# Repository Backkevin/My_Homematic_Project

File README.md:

# My_Homematic_Project

 My Homematic boards

-----------------------------------------------------------------

+ [HB-Dis-EP-42BW](https://github.com/Backkevin/My_Homematic_Project/tree/master/HB-Dis-EP-42BW)
+ [Nachbau von Jérôme](https://github.com/jp112sdl/HB-Dis-EP-42BW)
	+ V1.0
		* Work 50%
		* Partlist not OK
		* 230VAC Version
		* [INO FILE](https://github.com/Backkevin/My_Homematic_Project/tree/master/HB-Dis-EP-42BW/INO/HB-Dis-EP-42BW)
		* [GERBER FILES](https://github.com/Backkevin/My_Homematic_Project/tree/master/HB-Dis-EP-42BW/GERBER%20FILES)
		* [EAGLE FILES](https://github.com/Backkevin/My_Homematic_Project/tree/master/HB-Dis-EP-42BW/EAGLE)
		
	+ Work in progress !
>

-----------------------------------------------------------------

+ [HB-OU-MP3-LED](https://github.com/Backkevin/My_Homematic_Project/tree/master/HB-OU-MP3-LED)
+ [Nachbau von Jérôme](https://github.com/jp112sdl/HB-OU-MP3-LED)
	+ V2.1
		* Work 85%
		* Partlist OK
		* 230VAC Version
		* [INO FILE](https://github.com/Backkevin/My_Homematic_Project/tree/master/HB-OU-MP3-LED/INO/HB-OU-MP3-LED)
		* [GERBER FILES](https://github.com/Backkevin/My_Homematic_Project/tree/master/HB-OU-MP3-LED/GERBER%20FILES)
		* [EAGLE FILES](https://github.com/Backkevin/My_Homematic_Project/tree/master/HB-OU-MP3-LED/EAGLE)
		
	+ Work in progress !
>

-----------------------------------------------------------------

+ [HB-UNI-SenAct-4-4-RC](https://github.com/Backkevin/My_Homematic_Project/tree/master/HB-UNI-SenAct-4-4-RC)
+ [Nachbau von Ronny](https://github.com/ronnythomas/HB-UNI-SenAct-4-4-Hutschiene)
	+ V3.0
		* Work 100%
		* Partlist OK
		* 230VAC Version
		* [INO FILE](https://github.com/Backkevin/My_Homematic_Project/tree/master/HB-UNI-SenAct-4-4-RC/INO/HB-UNI-SenAct-4-4-RC)
		* [GERBER FILES](https://github.com/Backkevin/My_Homematic_Project/tree/master/HB-UNI-SenAct-4-4-RC/GERBER%20FILES)
		* [EAGLE FILES](https://github.com/Backkevin/My_Homematic_Project/tree/master/HB-UNI-SenAct-4-4-RC/EAGLE)
		
	+ Work in progress !
>

-----------------------------------------------------------------

+ [HB-UNI-SenAct-8-8-RC](https://github.com/Backkevin/My_Homematic_Project/tree/master/HB-UNI-SenAct-8-8-RC)
+ [Nachbau von Ronny](https://github.com/ronnythomas/HB-UNI-SenAct-8-8-Hutschiene)
	+ V2.1
		* Work 85%
		* Partlist OK
		* [INO FILE](https://github.com/Backkevin/My_Homematic_Project/tree/master/HB-UNI-SenAct-8-8-RC/INO/HB-UNI-SenAct-8-8-RC)
		* [GERBER FILES](https://github.com/Backkevin/My_Homematic_Project/tree/master/HB-UNI-SenAct-8-8-RC/GERBER%20FILES)
		* [EAGLE FILES](https://github.com/Backkevin/My_Homematic_Project/tree/master/HB-UNI-SenAct-8-8-RC/EAGLE)
		
	+ Work in progress !
>

-----------------------------------------------------------------

+ [HB-UNI-SEN-CAP-MOIST](https://github.com/Backkevin/My_Homematic_Project/tree/master/HB-UNI-SEN-CAP-MOIST)
+ [Nachbau von Jérôme](https://github.com/jp112sdl/HB-UNI-Sen-CAP-MOIST)
     + V1.2
		* Work 75%
		* Partlist not OK
		* 230VAC Version
		* [INO FILE](https://github.com/Backkevin/My_Homematic_Project/tree/master/HB-UNI-SEN-CAP-MOIST/INO/HB-UNI-SEN-CAP-MOIST)
		* [GERBER FILES](https://github.com/Backkevin/My_Homematic_Project/tree/master/HB-UNI-SEN-CAP-MOIST/GERBER%20FILES)
		* [EAGLE FILES](https://github.com/Backkevin/My_Homematic_Project/tree/master/HB-UNI-SEN-CAP-MOIST/EAGLE)		
		
	+ Work in progress !
>

+ [Nachbau von technikkram](https://technikkram.net/2019/05/anleitung-diy-feuchtigkeitssensor-fuer-gartenbewaesserung-bausatz-homematic)
	+ V0.5
		* Work 25%
		* Solar Version
		* Partlist not OK	
			
	+ Work in progress !
>

-----------------------------------------------------------------

+ [HB-UNI-SEN-PHO](https://github.com/Backkevin/My_Homematic_Project/tree/master/HB-UNI-SEN-PHO)
+ [Eigenbau]
	+ V1.0
		* Work 25%
		* Partlist not OK
		* 230VAC Version
		* [INO FILE](https://github.com/Backkevin/My_Homematic_Project/tree/master/HB-UNI-SEN-PHO/INO/HB-UNI-SEN-PHO)
		* [GERBER FILES](https://github.com/Backkevin/My_Homematic_Project/tree/master/HB-UNI-SEN-PHO/GERBER%20FILES)
		* [EAGLE FILES](https://github.com/Backkevin/My_Homematic_Project/tree/master/HB-UNI-SEN-PHO/EAGLE)
		
	+ Work in progress !
>

-----------------------------------------------------------------

+ [HB-UNI-Sen-RFID-RC](https://github.com/Backkevin/My_Homematic_Project/tree/master/HB-UNI-Sen-RFID-RC)
+ [Nachbau von Jérôme](https://github.com/jp112sdl/HB-UNI-Sen-RFID-RC)
	+ V1.0
		* Work 25%
		* Partlist not OK
		* 230VAC Version
		* [INO FILE](https://github.com/Backkevin/My_Homematic_Project/tree/master/HB-UNI-Sen-RFID-RC/INO/HB-UNI-Sen-RFID-RC)
		* [GERBER FILES](https://github.com/Backkevin/My_Homematic_Project/tree/master/HB-UNI-Sen-RFID-RC/GERBER%20FILES)
		* [EAGLE FILES](https://github.com/Backkevin/My_Homematic_Project/tree/master/HB-UNI-Sen-RFID-RC/EAGLE)
		
	+ Work in progress !
>

-----------------------------------------------------------------

+ [HB-UNI-Sen-TEMP-DS18B20](https://github.com/Backkevin/My_Homematic_Project/tree/master/HB-UNI-Sen-TEMP-DS18B20)
+ [Nachbau von Jérôme](https://github.com/jp112sdl/HB-UNI-Sen-TEMP-DS18B20)
	+ V1.0
		* Work 75%
		* Partlist not OK
		* 230VAC Version
		* [INO FILE](https://github.com/Backkevin/My_Homematic_Project/tree/master/HB-UNI-Sen-TEMP-DS18B20/INO/HB-UNI-Sen-TEMP-DS18B20)
		* [GERBER FILES](https://github.com/Backkevin/My_Homematic_Project/tree/master/HB-UNI-Sen-TEMP-DS18B20/GERBER%20FILES)
		* [EAGLE FILES](https://github.com/Backkevin/My_Homematic_Project/tree/master/HB-UNI-Sen-TEMP-DS18B20/EAGLE)
		
	+ Work in progress !
>

-----------------------------------------------------------------

+ [HB-UNI-Sen-WEIGHT](https://github.com/Backkevin/My_Homematic_Project/tree/master/HB-UNI-Sen-WEIGHT)
+ [Nachbau von Jérôme](https://github.com/jp112sdl/HB-UNI-Sen-WEIGHT)
	+ V1.0
		* Work 50%
		* Partlist not OK
		* 230VAC Version
		* [INO FILE](https://github.com/Backkevin/My_Homematic_Project/tree/master/HB-UNI-Sen-WEIGHT/INO/HB-UNI-Sen-WEIGHT)
		* [GERBER FILES](https://github.com/Backkevin/My_Homematic_Project/tree/master/HB-UNI-Sen-WEIGHT/GERBER%20FILES)
		* [EAGLE FILES](https://github.com/Backkevin/My_Homematic_Project/tree/master/HB-UNI-Sen-WEIGHT/EAGLE)
		
	+ Work in progress !
>

-----------------------------------------------------------------

+ [HM-ES-PMSw1-Pl_GosundSP1](https://github.com/Backkevin/My_Homematic_Project/tree/master/HM-ES-PMSw1-Pl_GosundSP1)
+ [Nachbau von Jérôme](https://github.com/jp112sdl/Beispiel_AskSinPP/tree/master/examples/HM-ES-PMSw1-Pl_GosundSP1)
	+ V1.3
		* Work 50%
		* Partlist not OK
		* 230VAC Version
		* [INO FILE](https://github.com/Backkevin/My_Homematic_Project/tree/master/HM-ES-PMSw1-Pl_GosundSP1/INO/HM-ES-PMSw1-Pl_GosundSP1)
		* [GERBER FILES](https://github.com/Backkevin/My_Homematic_Project/tree/master/HM-ES-PMSw1-Pl_GosundSP1/GERBER%20FILES)
		* [EAGLE FILES](https://github.com/Backkevin/My_Homematic_Project/tree/master/HM-ES-PMSw1-Pl_GosundSP1/EAGLE)
		
	+ Work in progress !
>

-----------------------------------------------------------------

+ [HM-SEC-MDIR](https://github.com/Backkevin/My_Homematic_Project/tree/master/HM-SEC-MDIR)
+ [Nachbau von Jérôme](https://asksinpp.de/Projekte/jan/HM-SEC-MDIR/)
	+ V0.0
		* Work 0%
		* Partlist not OK
		* 230VAC Version
		* [INO FILE](https://github.com/Backkevin/My_Homematic_Project/tree/master/HM-SEC-MDIR/INO/HM-SEC-MDIR)
		* [GERBER FILES](https://github.com/Backkevin/My_Homematic_Project/tree/master/HM-SEC-MDIR/GERBER%20FILES)
		* [EAGLE FILES](https://github.com/Backkevin/My_Homematic_Project/tree/master/HM-SEC-MDIR/EAGLE)
		
	+ Work in progress !
>

-----------------------------------------------------------------

+ [HM-MOUSETRAP](https://github.com/Backkevin/My_Homematic_Project/tree/master/HM-MOUSETRAP)
+ [Eigenbau]
	+ V0.5
		* Work 25%
		* Battery Version
		* Partlist not OK
		* [STL Parts not OK](https://github.com/Backkevin/My_Homematic_Project/tree/master/HM-MOUSETRAP/STL%20FILES)
		* [INO FILE](https://github.com/Backkevin/My_Homematic_Project/tree/master/HM-MOUSETRAP/HM-MOUSETRAP)
		* [GERBER FILES](https://github.com/Backkevin/My_Homematic_Project/tree/master/HM-MOUSETRAP/GERBER%20FILES)
		* [EAGLE FILES](https://github.com/Backkevin/My_Homematic_Project/tree/master/HM-MOUSETRAP/EAGLE)
		
	+ Work in progress !
>

-----------------------------------------------------------------

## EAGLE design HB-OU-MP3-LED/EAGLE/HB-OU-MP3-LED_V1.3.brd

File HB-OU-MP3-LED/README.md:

# HB-OU-MP3-LED

+ HB-OU-MP3-LED
	+ V2.1
		* Work 85%
		* 230VAC Version
		* Partlist OK
	+ Work in progress !
>

### Partslist 230VAC Version
                    
  Part Name   |      PIC      |   Part Info   | Part Quantity |   Part Link 
------------- | ------------- | ------------- | ------------- | -------------
Arduino||Arduino Pro Mini 8Mhz 3.3V|1|[Links](https://de.aliexpress.com/item/32863952987.html?spm=a2g0s.9042311.0.0.27424c4d2YDzey)
CC1101||CC1101 Funkmodul|1|[Links](https://de.aliexpress.com/item/32924239954.html?spm=a2g0s.9042311.0.0.27424c4dO9ofu2)
Config,S1 - S4||Taster 6x6|5|[Links](https://de.aliexpress.com/item/32912263133.html?spm=a2g0s.9042311.0.0.2cb44c4dtuowdv)
LED1||LED 3mm|1|[Links](https://de.aliexpress.com/item/32844298998.html?spm=a2g0s.9042311.0.0.27424c4dBW9kvr)
HLK-5M05||HLK-PM01|1|[Links](https://de.aliexpress.com/item/32705471039.html?spm=a2g0s.9042311.0.0.2cb44c4dtuowdv)
F1,F2||Sicherungshalter|2|[Links](https://de.aliexpress.com/item/32817849786.html?spm=a2g0o.productlist.0.0.260073beDSkClD&algo_pvid=51b52a6f-dc94-4152-9721-98bffea40076&algo_expid=51b52a6f-dc94-4152-9721-98bffea40076-1&btsid=c94e558f-368d-470b-a49c-61c69230d3d9&ws_ab_test=searchweb0_0,searchweb201602_2,searchweb201603_52)
R5,R6||470 Ohm Widerstand|2|[Links](https://de.aliexpress.com/item/32475181535.html?spm=a2g0o.productlist.0.0.d4fa8034p2AKck&s=p&algo_pvid=4976c9e3-6165-4df4-b127-6d9845fdbe12&algo_expid=4976c9e3-6165-4df4-b127-6d9845fdbe12-1&btsid=7a52ff49-9ff4-47d2-965f-007ad481e8b7&ws_ab_test=searchweb0_0,searchweb201602_2,searchweb201603_52)
230V,HP||Wannenstecker für AKL 249, 2-pol, RM5,08|2|[Links](https://www.reichelt.de/wannenstecker-fuer-akl-249-2-pol-rm5-08-akl-230-02-p36701.html?)
RL1||Wannenstecker für AKL 249, 3-pol, RM5,08|1|[Links](https://www.reichelt.de/wannenstecker-fuer-akl-249-3-pol-rm5-08-akl-230-03-p36702.html?)
RL1||relais srd-05vdc|1|[Links](https://de.aliexpress.com/item/32695798177.html?spm=a2g0o.productlist.0.0.46db7659cuB4fB&algo_pvid=f16bd12e)
Arduino||Pin Header Streifen 12 Pin|2|[Links](https://de.aliexpress.com/item/32904918519.html?spm=a2g0s.9042311.0.0.27424c4dCsKCBi)
CC1101||Stiftleiste 20 polig, vergoldet, Raster 2,00mm|1|[Links](https://secure.reichelt.com/lu/de/stiftleiste-20-pol-vergoldet-bkl-10120400-p235635.html?)
C1||50V10UF|1|[Links](https://de.aliexpress.com/item/32741687066.html?spm=a2g0o.productlist.0.0.4d225216N68Cr1&algo_pvid=dbcb75f4-e623-4355-8aa4-ccd3a7b65d32&algo_expid=dbcb75f4-e623-4355-8aa4-ccd3a7b65d32-3&btsid=a9b8176e-1372-45d7-a781-8d3fc9fab8e5&ws_ab_test=searchweb0_0,searchweb201602_2,searchweb201603_52)
Arduino||Jumper|1|[Links](https://de.aliexpress.com/item/32873263301.html?spm=a2g0o.productlist.0.0.18ea263dluRsmQ&algo_pvid=b495ebad-e4de-4809-a086-8143c1f9f12b&algo_expid=b495ebad-e4de-4809-a086-8143c1f9f12b-2&btsid=53bb7c29-6fd7-4471-b8c4-bc2766b36d10&ws_ab_test=searchweb0_0,searchweb201602_2,searchweb201603_52)
RGB||RGB LED Ring 12 Bits WS2812|1|[Links](https://de.aliexpress.com/item/32668049892.html?spm=a2g0s.9042311.0.0.27424c4dPLs0SQ)
-||Speicher Karte|1|[Links](https://de.aliexpress.com/item/4000019505752.html?gps-id=detail404&scm=1007.16891.96945.0&scm_id=1007.16891.96945.0&scm-url=1007.16891.96945.0&pvid=281247d2-c3f0-421b-91d9-69d1a5222bc4)
DFP||DFPlayer|1|[Links](https://de.aliexpress.com/item/32750446150.html?spm=a2g0s.9042311.0.0.5daf4c4dPxve55)
R2,R3,R4||1K Ohm Widerstand|3|[Links](https://de.aliexpress.com/item/32475181535.html?spm=a2g0o.productlist.0.0.d4fa8034p2AKck&s=p&algo_pvid=4976c9e3-6165-4df4-b127-6d9845fdbe12&algo_expid=4976c9e3-6165-4df4-b127-6d9845fdbe12-1&btsid=7a52ff49-9ff4-47d2-965f-007ad481e8b7&ws_ab_test=searchweb0_0,searchweb201602_2,searchweb201603_52)
R5||10K Ohm Widerstand|1|[Links](https://de.aliexpress.com/item/32475181535.html?spm=a2g0o.productlist.0.0.d4fa8034p2AKck&s=p&algo_pvid=4976c9e3-6165-4df4-b127-6d9845fdbe12&algo_expid=4976c9e3-6165-4df4-b127-6d9845fdbe12-1&btsid=7a52ff49-9ff4-47d2-965f-007ad481e8b7&ws_ab_test=searchweb0_0,searchweb201602_2,searchweb201603_52)
D1||1N4007|1|[Links](https://de.aliexpress.com/item/32224555821.html?spm=a2g0o.productlist.0.0.6ff73c09BmbGrH&algo_pvid=0cedbead-f9df-432f-a6b8-7889af0010ea&algo_expid=0cedbead-f9df-432f-a6b8-7889af0010ea-0&btsid=9d3b584d-5993-438c-bda5-70eb309fc04f&ws_ab_test=searchweb0_0,searchweb201602_2,searchweb201603_52)
BC327||BC327|1|[Links](https://de.aliexpress.com/item/32694388198.html?spm=a2g0o.productlist.0.0.490b435cYT2xvd&algo_pvid=df4c990b-2fc8-4f12-b155-a7185f993490&algo_expid=df4c990b-2fc8-4f12-b155-a7185f993490-2&btsid=ff438d29-ef2e-467f-babc-337d85f9c973&ws_ab_test=searchweb0_0,searchweb201602_2,searchweb201603_52)
PC817||PC817|1|[Links](https://de.aliexpress.com/item/32835155712.html?spm=a2g0s.9042311.0.0.27424c4dyoIvyA)
-|-|-|-
OPTIONAL||FT232RL USB zu TTL Serielle Adapter|1|[Links](https://de.aliexpress.com/item/32846166237.html?spm=a2g0s.9042311.0.0.27424c4dQGznlY)
OPTIONAL||28X40 MM 4R 3 W lautsprecher|1|[Links](https://de.aliexpress.com/item/32765499972.html?spm=a2g0s.9042311.0.0.27424c4dS08YRH)

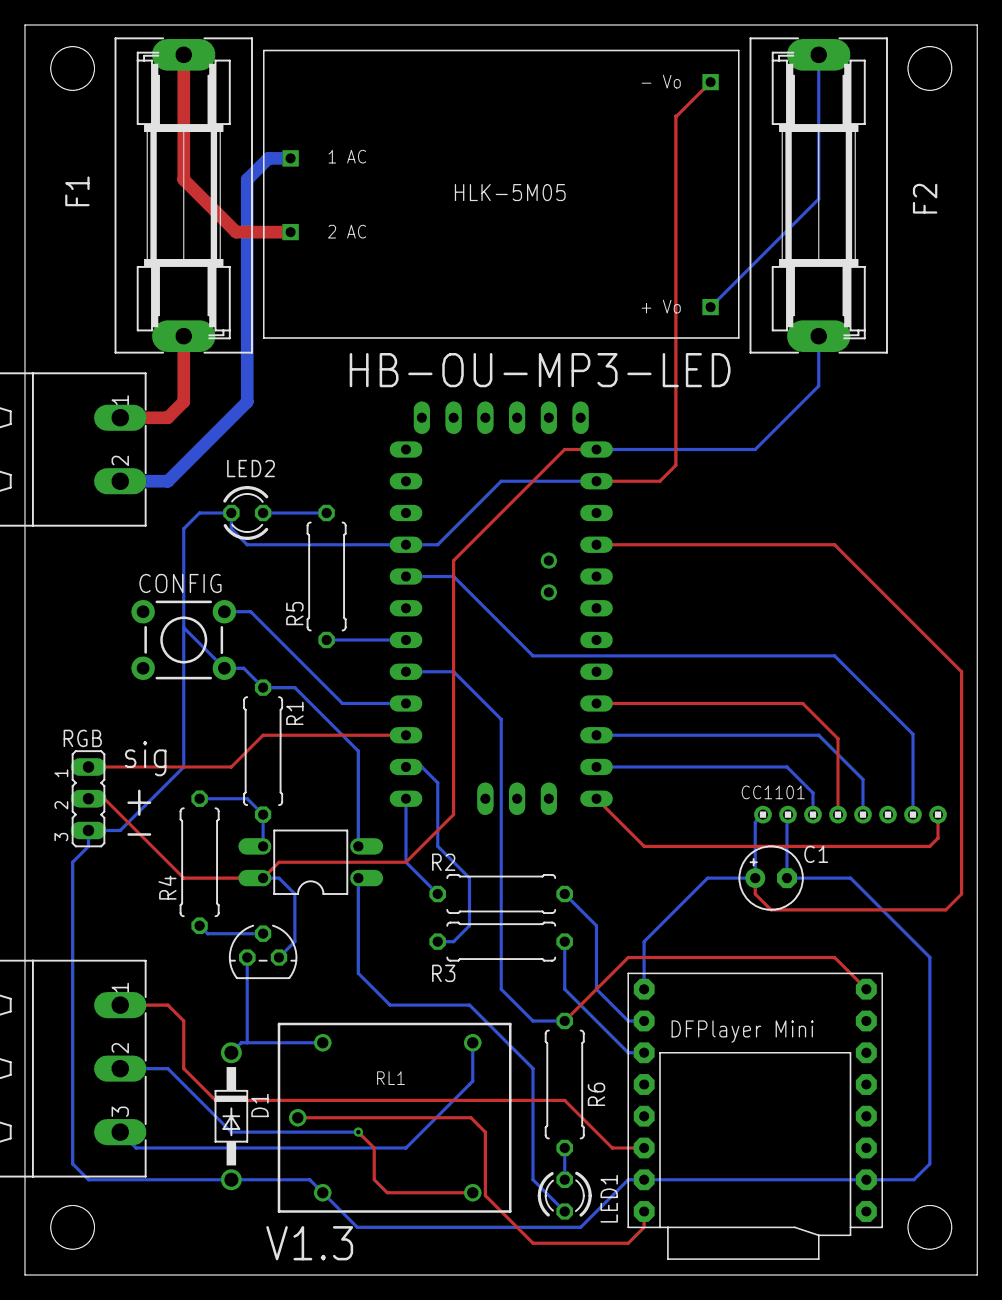
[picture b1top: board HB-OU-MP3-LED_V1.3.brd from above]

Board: 2 copper layers, 76.2 x 100.0 mm, 23 parts (0 on the bottom side), 30 nets.

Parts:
C1: E2,5-5
CONFIG: MOMENTARY-SWITCH-SPST-PTH-6.0MM-KIT; TACTILE_SWITCH_PTH_6.0MM_KIT
D1: 1N4007; DO41-10
F1, F2: SH22,5A
LED1, LED2: LED3MM
OK1: PC817; DIL04
Q1: BC327; TO92
R1: 10K; 0309/10
R2, R3, R4: 1K; 0309/10
R5, R6: 470; 0309/10
RGB: JP2
RL1: RELAYPTH; SRD-05VDC-SL-C
U$1: 1X8
U$2: ABK-PRO-MINI
U$3: 5VDC/5W; HLK-5M05
U$4: DFPLAYER
X1: MSTBA2
X3: MSTBA3

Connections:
CSN: U$1.8, U$2.D10
GDO0: U$1.7, U$2.D2
GND: C1.-, CONFIG.1, D1.A, LED2.A, OK1.2, R1.1, RGB.3, RL1.COIL0, U$1.2, U$2.GND, U$2.GND1, U$3.3, U$4.GND_1, U$4.GND_2
unnamed: RGB.1, U$2.D7
unnamed: CONFIG.3, U$2.D6
unnamed: R2.2, U$2.D9
unnamed: R3.2, U$2.D8
unnamed: R6.1, U$2.D5, U$4.BUSY
unnamed: U$4.SPK1, X3.1
unnamed: RL1.SWCOMMON, U$4.SPK2
unnamed: LED1.A, R6.2
unnamed: F1.1, X1.1
unnamed: F2.1, U$3.4
unnamed: U$3.2, X1.2
unnamed: D1.C, Q1.3, RL1.COIL1
unnamed: RL1.SWCLOSED, X3.2
unnamed: R2.1, U$4.RX
unnamed: R3.1, U$4.TX
unnamed: OK1.3, R1.2, R4.1
unnamed: R5.1, U$2.D4
unnamed: LED2.K, R5.2
unnamed: F1.2, U$3.1
unnamed: RL1.SWOPEN, X3.3
unnamed: LED1.K, OK1.1
unnamed: Q1.2, R4.2
RAW: F2.2, OK1.4, Q1.1, RGB.2, U$2.RAW
SCLK: U$1.4, U$2.D13
SI: U$1.3, U$2.D11
SO: U$1.5, U$2.D12
VCC: C1.+, U$1.1, U$2.VCC, U$4.VCC

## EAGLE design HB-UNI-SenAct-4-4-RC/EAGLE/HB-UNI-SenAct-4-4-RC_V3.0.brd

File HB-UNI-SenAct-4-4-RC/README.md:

# HB-UNI-SenAct-4-4-RC

+ HB-UNI-SenAct-4-4-RC
	+ V3.0
		* Work 100%
		* 230VAC Version
		* Partlist OK
	+ Work in progress !

>

### Partslist 230VAC Version
                    
  Part Name   |      PIC      |   Part Info   | Part Quantity |   Part Link 
------------- | ------------- | ------------- | ------------- | -------------
Arduino||Arduino Pro Mini 8Mhz 3.3V|1|[Links](https://de.aliexpress.com/item/32863952987.html?spm=a2g0s.9042311.0.0.27424c4d2YDzey)
CC1101||CC1101 Funkmodul|1|[Links](https://de.aliexpress.com/item/32924239954.html?spm=a2g0s.9042311.0.0.27424c4dO9ofu2)
Config,S1 - S4||Taster 6x6|5|[Links](https://de.aliexpress.com/item/32912263133.html?spm=a2g0s.9042311.0.0.2cb44c4dtuowdv)
LED1 - LED5||LED 3mm|5|[Links](https://de.aliexpress.com/item/32844298998.html?spm=a2g0s.9042311.0.0.27424c4dBW9kvr)
HLK-5M05||HLK-PM01|1|[Links](https://de.aliexpress.com/item/32705471039.html?spm=a2g0s.9042311.0.0.2cb44c4dtuowdv)
F1,F2||Sicherungshalter|2|[Links](https://de.aliexpress.com/item/32817849786.html?spm=a2g0o.productlist.0.0.260073beDSkClD&algo_pvid=51b52a6f-dc94-4152-9721-98bffea40076&algo_expid=51b52a6f-dc94-4152-9721-98bffea40076-1&btsid=c94e558f-368d-470b-a49c-61c69230d3d9&ws_ab_test=searchweb0_0,searchweb201602_2,searchweb201603_52)
R1 - R5||470 Ohm Widerstand|5|[Links](https://de.aliexpress.com/item/32475181535.html?spm=a2g0o.productlist.0.0.d4fa8034p2AKck&s=p&algo_pvid=4976c9e3-6165-4df4-b127-6d9845fdbe12&algo_expid=4976c9e3-6165-4df4-b127-6d9845fdbe12-1&btsid=7a52ff49-9ff4-47d2-965f-007ad481e8b7&ws_ab_test=searchweb0_0,searchweb201602_2,searchweb201603_52)
230V,S1 - S4||Wannenstecker für AKL 249, 2-pol, RM5,08|5|[Links](https://www.reichelt.de/wannenstecker-fuer-akl-249-2-pol-rm5-08-akl-230-02-p36701.html?)
RL1 - RL4||Wannenstecker für AKL 249, 3-pol, RM5,08|4|[Links](https://www.reichelt.de/wannenstecker-fuer-akl-249-3-pol-rm5-08-akl-230-03-p36702.html?)
RL1 - RL4||relais srd-05vdc|4|[Links](https://de.aliexpress.com/item/32695798177.html?spm=a2g0o.productlist.0.0.46db7659cuB4fB&algo_pvid=f16bd12e)
Arduino||Pin Header Streifen 12 Pin|2|[Links](https://de.aliexpress.com/item/32904918519.html?spm=a2g0s.9042311.0.0.27424c4dCsKCBi)
CC1101||Stiftleiste 20 polig, vergoldet, Raster 2,00mm|1|[Links](https://secure.reichelt.com/lu/de/stiftleiste-20-pol-vergoldet-bkl-10120400-p235635.html?)
ULN2803||ULN2803A|1|[Links](https://de.aliexpress.com/item/32881616806.html?spm=a2g0o.productlist.0.0.27805012dPDPf4&algo_pvid=2ce275e5-5ca6-4441-a1e3-fb3df6923537&algo_expid=2ce275e5-5ca6-4441-a1e3-fb3df6923537-0&btsid=14cad76a-3ab1-4af8-af47-443eb0bf5dae&ws_ab_test=searchweb0_0,searchweb201602_2,searchweb201603_52)
C1||50V10UF|1|[Links](https://de.aliexpress.com/item/32741687066.html?spm=a2g0o.productlist.0.0.4d225216N68Cr1&algo_pvid=dbcb75f4-e623-4355-8aa4-ccd3a7b65d32&algo_expid=dbcb75f4-e623-4355-8aa4-ccd3a7b65d32-3&btsid=a9b8176e-1372-45d7-a781-8d3fc9fab8e5&ws_ab_test=searchweb0_0,searchweb201602_2,searchweb201603_52)
Sabotage,Arduino||Jumper|1|[Links](https://de.aliexpress.com/item/32873263301.html?spm=a2g0o.productlist.0.0.18ea263dluRsmQ&algo_pvid=b495ebad-e4de-4809-a086-8143c1f9f12b&algo_expid=b495ebad-e4de-4809-a086-8143c1f9f12b-2&btsid=53bb7c29-6fd7-4471-b8c4-bc2766b36d10&ws_ab_test=searchweb0_0,searchweb201602_2,searchweb201603_52)
-|-|-|-
OPTIONAL||FT232RL USB zu TTL Serielle Adapter|1|[Links](https://de.aliexpress.com/item/32846166237.html?spm=a2g0s.9042311.0.0.27424c4dQGznlY)

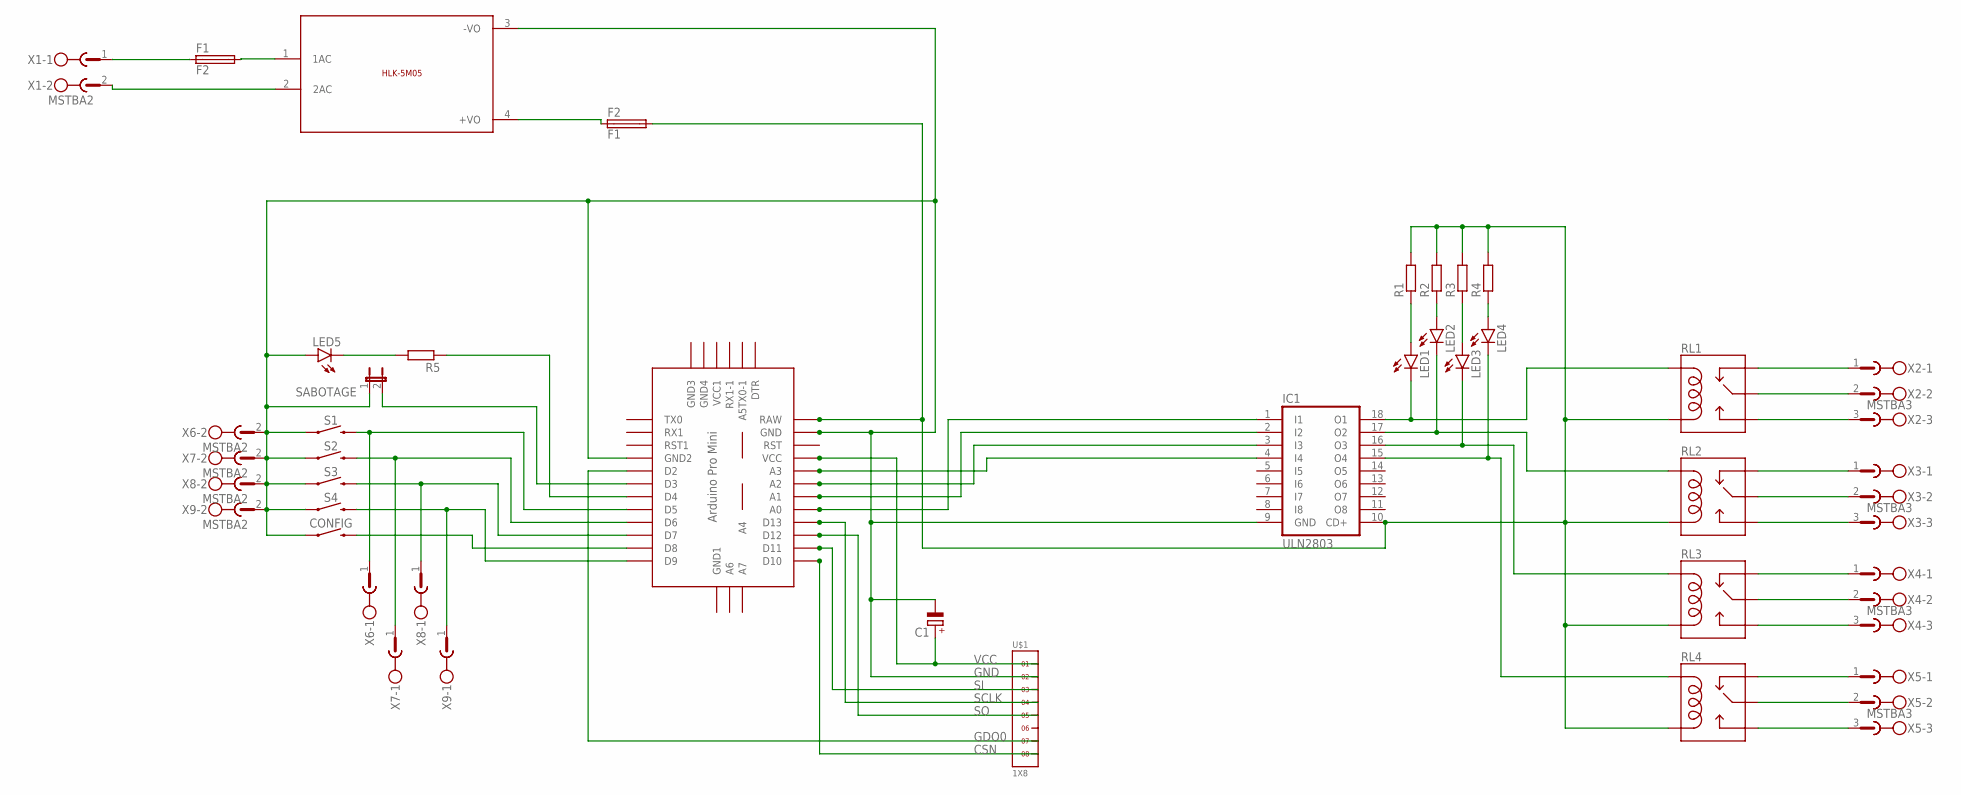
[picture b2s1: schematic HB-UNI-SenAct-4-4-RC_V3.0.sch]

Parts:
C1: CPOL-EUE2.5-5; E2,5-5
CONFIG: MOMENTARY-SWITCH-SPST-PTH-6.0MM-KIT; TACTILE_SWITCH_PTH_6.0MM_KIT
F1: F2; SH22,5A
F2: F1; SH22,5A
IC1: ULN2803; DIL18
LED1, LED2, LED3, LED4, LED5: LED3MM
R1, R2, R3, R4, R5: R-EU_0309/10; 0309/10
RL1, RL3, RL4: RELAYPTH; SRD-05VDC-SL-C
RL2: RL2; SRD-05VDC-SL-C
S1: MOMENTARY-SWITCH-SPST-PTH-6.0MM; TACTILE_SWITCH_PTH_6.0MM
S2, S3, S4: MOMENTARY-SWITCH-SPST-PTH-6.0MM-KIT; TACTILE_SWITCH_PTH_6.0MM_KIT
SABOTAGE: JP1E; JP1
U$1: 1X8
U$2: ABK-PRO-MINI
U$3: 5VDC/5W; HLK-5M05
X1, X6, X7, X8, X9: MSTBA2
X2, X3, X4, X5: MSTBA3

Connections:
CSN: U$1.8, U$2.D10
GDO0: U$1.7, U$2.D2
GND: C1.-, CONFIG.1, IC1.9 (GND), LED5.A, S1.1, S2.1, S3.1, S4.1, SABOTAGE.1, U$1.2, U$2.GND, U$2.GND1 (GND2), U$3.3 (-VO), X6.2, X7.2, X8.2, X9.2
unnamed: IC1.1 (I1), U$2.A0
unnamed: IC1.2 (I2), U$2.A1
unnamed: IC1.3 (I3), U$2.A2
unnamed: IC1.4 (I4), U$2.A3
unnamed: LED1.A, R1.1
unnamed: LED2.A, R2.1
unnamed: LED3.A, R3.1
unnamed: LED4.A, R4.1
unnamed: F1.1, X1.1
unnamed: F2.1, U$3.4 (+VO)
unnamed: U$3.2 (2AC), X1.2
unnamed: S1.3 (2), U$2.D5, X6.1
unnamed: S2.3 (2), U$2.D6, X7.1
unnamed: S3.3 (2), U$2.D7, X8.1
unnamed: S4.3 (2), U$2.D9, X9.1
unnamed: CONFIG.3 (2), U$2.D8
unnamed: R5.1, U$2.D4
unnamed: LED5.K (C), R5.2
unnamed: F1.2, U$3.1 (1AC)
unnamed: SABOTAGE.2, U$2.D3
unnamed: RL3.SWCLOSED (SWCLOSE), X4.1
unnamed: RL4.SWCOMMON, X5.2
unnamed: RL3.SWOPEN, X4.3
unnamed: F2.2, IC1.10 (CD+), R1.2, R2.2, R3.2, R4.2, RL1.COIL0, RL2.COIL0, RL3.COIL0, RL4.COIL0, U$2.RAW
unnamed: RL4.SWCLOSED (SWCLOSE), X5.1
unnamed: RL3.SWCOMMON, X4.2
unnamed: RL4.SWOPEN, X5.3
unnamed: RL2.SWOPEN, X3.3
unnamed: RL2.SWCOMMON, X3.2
unnamed: RL2.SWCLOSED (SWCLOSE), X3.1
unnamed: RL1.SWOPEN, X2.3
unnamed: RL1.SWCOMMON, X2.2
unnamed: RL1.SWCLOSED (SWCLOSE), X2.1
unnamed: IC1.18 (O1), LED1.K (C), RL1.COIL1
unnamed: IC1.17 (O2), LED2.K (C), RL2.COIL1
unnamed: IC1.16 (O3), LED3.K (C), RL3.COIL1
unnamed: IC1.15 (O4), LED4.K (C), RL4.COIL1
SCLK: U$1.4, U$2.D13
SI: U$1.3, U$2.D11
SO: U$1.5, U$2.D12
VCC: C1.+, U$1.1, U$2.VCC

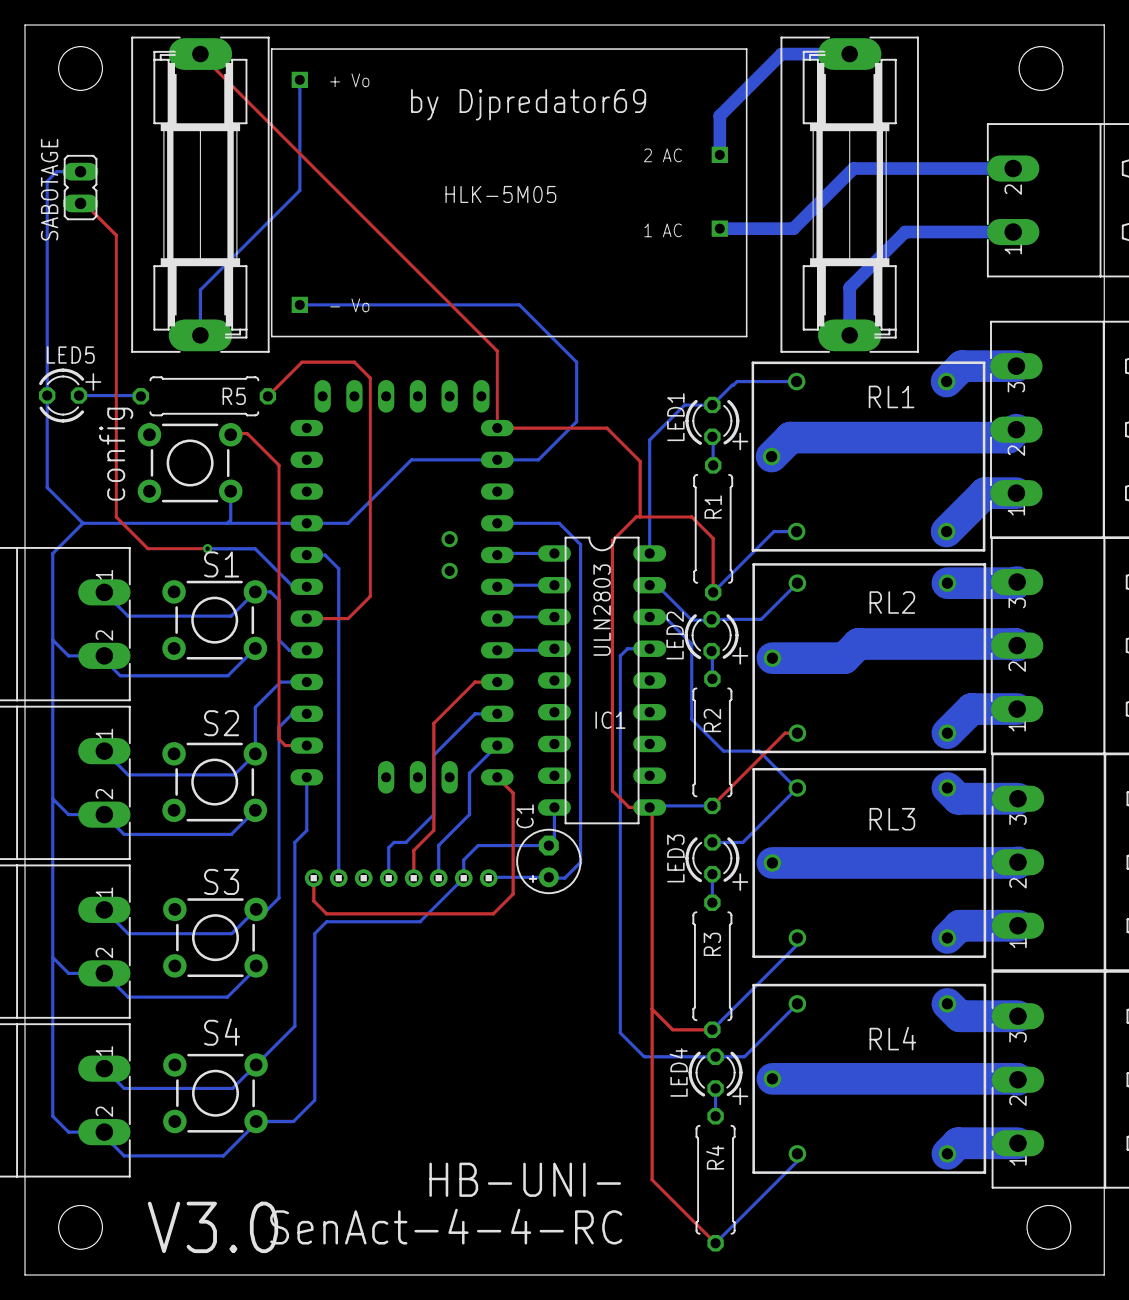
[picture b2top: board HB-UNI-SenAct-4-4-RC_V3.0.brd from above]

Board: 2 copper layers, 86.3 x 100.0 mm, 36 parts (0 on the bottom side), 44 nets.

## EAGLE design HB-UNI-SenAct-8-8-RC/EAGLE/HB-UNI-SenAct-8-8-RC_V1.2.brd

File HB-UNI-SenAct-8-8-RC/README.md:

# HB-UNI-SenAct-8-8-RC

+ HB-UNI-SenAct-8-8-RC
	+ V2.1
		* Work 85%
		* 230VAC Version
		* Partlist OK
	+ Work in progress !
>

### Partslist 230VAC Version
                    
  Part Name   |      PIC      |   Part Info   | Part Quantity |   Part Link 
------------- | ------------- | ------------- | ------------- | -------------
Arduino||Arduino Pro Mini 8Mhz 3.3V|1|[Links](https://de.aliexpress.com/item/32863952987.html?spm=a2g0s.9042311.0.0.27424c4d2YDzey)
CC1101||CC1101 Funkmodul|1|[Links](https://de.aliexpress.com/item/32924239954.html?spm=a2g0s.9042311.0.0.27424c4dO9ofu2)
Config,S1 - S8||Taster 6x6|9|[Links](https://de.aliexpress.com/item/32912263133.html?spm=a2g0s.9042311.0.0.2cb44c4dtuowdv)
LED1 - LED9||LED 3mm|9|[Links](https://de.aliexpress.com/item/32844298998.html?spm=a2g0s.9042311.0.0.27424c4dBW9kvr)
HLK-5M05||HLK-PM01|1|[Links](https://de.aliexpress.com/item/32705471039.html?spm=a2g0s.9042311.0.0.2cb44c4dtuowdv)
F1,F2||Sicherungshalter|2|[Links](https://de.aliexpress.com/item/32817849786.html?spm=a2g0o.productlist.0.0.260073beDSkClD&algo_pvid=51b52a6f-dc94-4152-9721-98bffea40076&algo_expid=51b52a6f-dc94-4152-9721-98bffea40076-1&btsid=c94e558f-368d-470b-a49c-61c69230d3d9&ws_ab_test=searchweb0_0,searchweb201602_2,searchweb201603_52)
R1 - R9||470 Ohm Widerstand|9|[Links](https://de.aliexpress.com/item/32475181535.html?spm=a2g0o.productlist.0.0.d4fa8034p2AKck&s=p&algo_pvid=4976c9e3-6165-4df4-b127-6d9845fdbe12&algo_expid=4976c9e3-6165-4df4-b127-6d9845fdbe12-1&btsid=7a52ff49-9ff4-47d2-965f-007ad481e8b7&ws_ab_test=searchweb0_0,searchweb201602_2,searchweb201603_52)
230V||Wannenstecker für AKL 249, 2-pol, RM5,08|1|[Links](https://www.reichelt.de/wannenstecker-fuer-akl-249-2-pol-rm5-08-akl-230-02-p36701.html?)
RL1 - RL8||Wannenstecker für AKL 249, 3-pol, RM5,08|8|[Links](https://www.reichelt.de/wannenstecker-fuer-akl-249-3-pol-rm5-08-akl-230-03-p36702.html?)
RL1 - RL8||relais srd-05vdc|8|[Links](https://de.aliexpress.com/item/32695798177.html?spm=a2g0o.productlist.0.0.46db7659cuB4fB&algo_pvid=f16bd12e)
Arduino||Pin Header Streifen 12 Pin|3|[Links](https://de.aliexpress.com/item/32904918519.html?spm=a2g0s.9042311.0.0.27424c4dCsKCBi)
CC1101||Stiftleiste 20 polig, vergoldet, Raster 2,00mm|1|[Links](https://secure.reichelt.com/lu/de/stiftleiste-20-pol-vergoldet-bkl-10120400-p235635.html?)
74AC540N||74AC540N|1|[Links](https://de.aliexpress.com/item/32962771569.html?spm=a2g0s.9042311.0.0.27424c4d9oXxJ5)
PCF8574||PCF8574|1|[Links](https://de.aliexpress.com/item/32933373566.html?spm=a2g0o.productlist.0.0.64a84f64Lvqpim&algo_pvid=cbe97703-3691-461b-ab85-9e0ba62d57db&algo_expid=cbe97703-3691-461b-ab85-9e0ba62d57db-1&btsid=dcfb9457-b3f3-4e03-af0e-92040a947379&ws_ab_test=searchweb0_0,searchweb201602_2,searchweb201603_52)
ULN2803||ULN2803A|1|[Links](https://de.aliexpress.com/item/32881616806.html?spm=a2g0o.productlist.0.0.27805012dPDPf4&algo_pvid=2ce275e5-5ca6-4441-a1e3-fb3df6923537&algo_expid=2ce275e5-5ca6-4441-a1e3-fb3df6923537-0&btsid=14cad76a-3ab1-4af8-af47-443eb0bf5dae&ws_ab_test=searchweb0_0,searchweb201602_2,searchweb201603_52)
C1||50V10UF|1|[Links](https://de.aliexpress.com/item/32741687066.html?spm=a2g0o.productlist.0.0.4d225216N68Cr1&algo_pvid=dbcb75f4-e623-4355-8aa4-ccd3a7b65d32&algo_expid=dbcb75f4-e623-4355-8aa4-ccd3a7b65d32-3&btsid=a9b8176e-1372-45d7-a781-8d3fc9fab8e5&ws_ab_test=searchweb0_0,searchweb201602_2,searchweb201603_52)
Sabotage,Arduino||Jumper|2|[Links](https://de.aliexpress.com/item/32873263301.html?spm=a2g0o.productlist.0.0.18ea263dluRsmQ&algo_pvid=b495ebad-e4de-4809-a086-8143c1f9f12b&algo_expid=b495ebad-e4de-4809-a086-8143c1f9f12b-2&btsid=53bb7c29-6fd7-4471-b8c4-bc2766b36d10&ws_ab_test=searchweb0_0,searchweb201602_2,searchweb201603_52)
-|-|-|-
OPTIONAL||FT232RL USB zu TTL Serielle Adapter|1|[Links](https://de.aliexpress.com/item/32846166237.html?spm=a2g0s.9042311.0.0.27424c4dQGznlY)

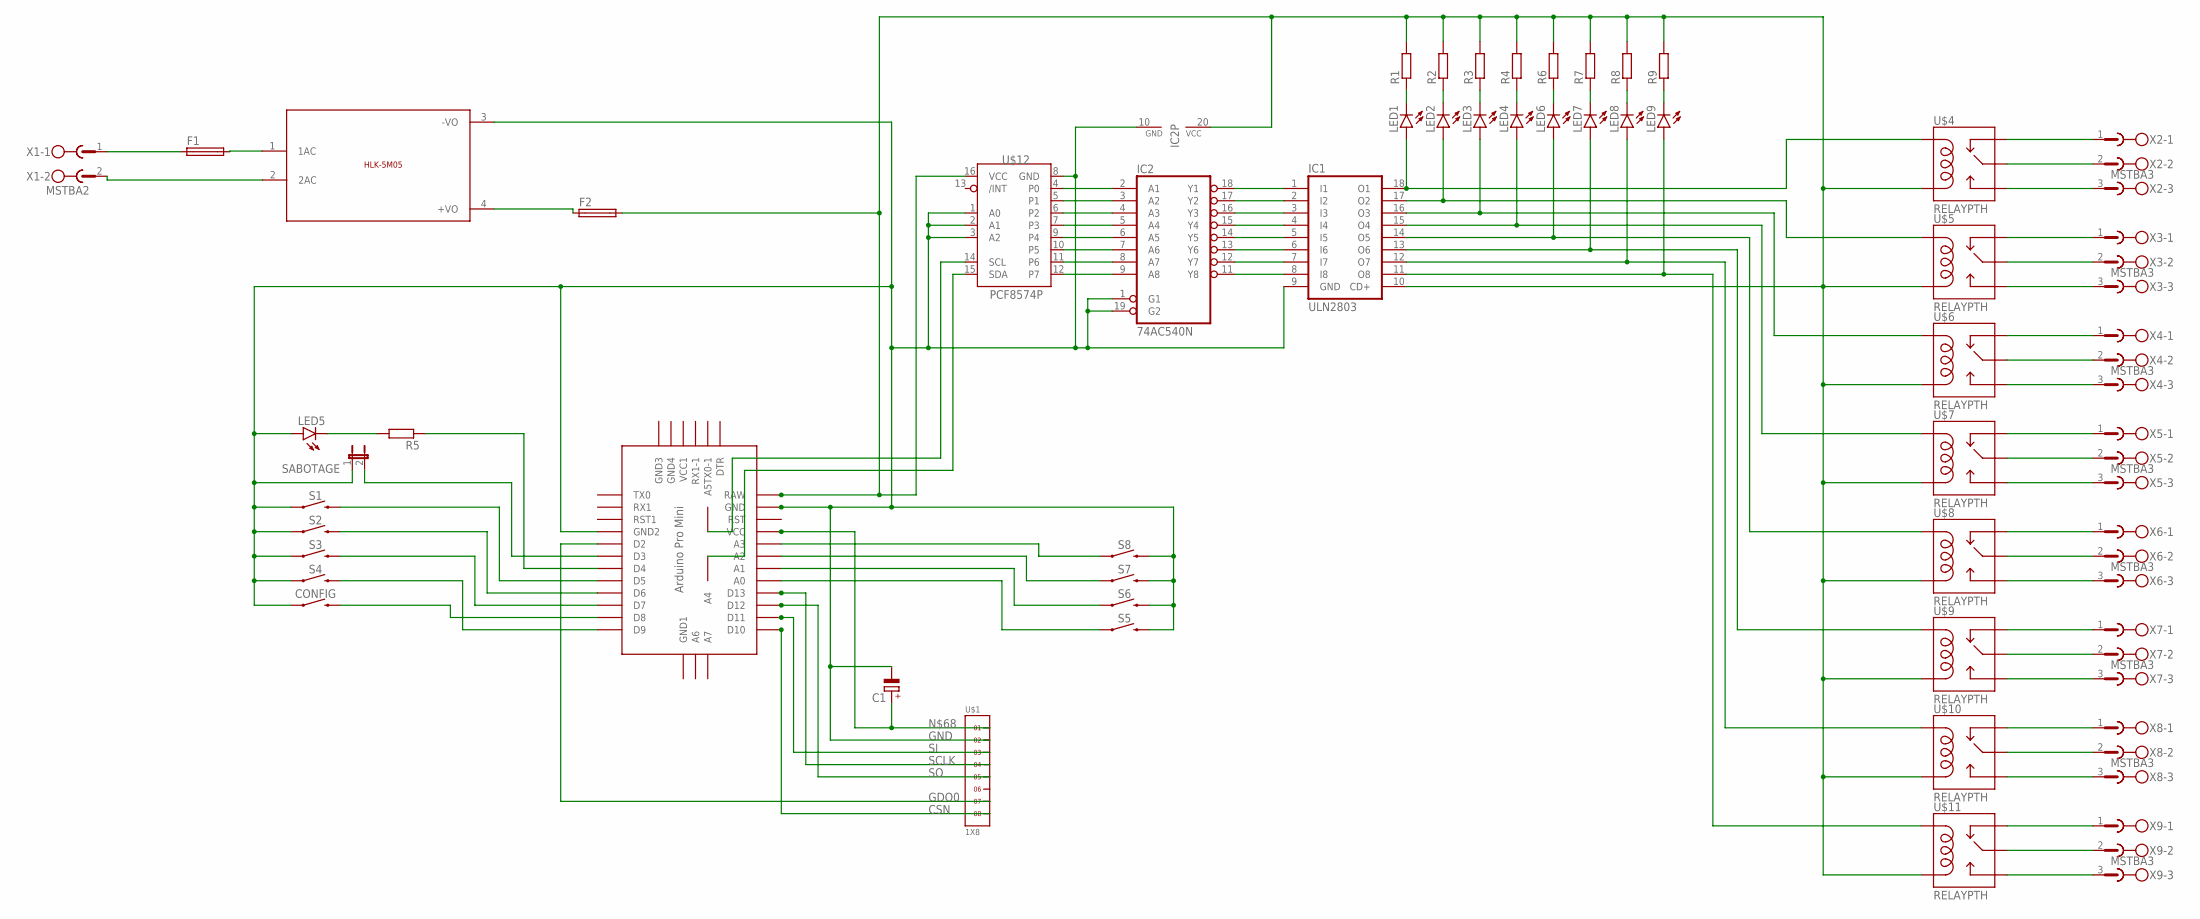
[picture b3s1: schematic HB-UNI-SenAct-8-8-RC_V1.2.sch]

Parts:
C1: CPOL-EUE2.5-5; E2,5-5
CONFIG: MOMENTARY-SWITCH-SPST-PTH-6.0MM-KIT; TACTILE_SWITCH_PTH_6.0MM_KIT
F1, F2: SH22,5A
IC1: ULN2803; DIL18
IC2: 74AC540N; DIL20
LED1, LED2, LED3, LED4, LED5, LED6, LED7, LED8, LED9: LED3MM
R1, R2, R3, R4, R5, R6, R7, R8, R9: R-EU_0309/10; 0309/10
S1: MOMENTARY-SWITCH-SPST-PTH-6.0MM; TACTILE_SWITCH_PTH_6.0MM
S2, S3, S4, S5, S6, S7, S8: MOMENTARY-SWITCH-SPST-PTH-6.0MM-KIT; TACTILE_SWITCH_PTH_6.0MM_KIT
SABOTAGE: JP1E; JP1
U$1: 1X8
U$2: ABK-PRO-MINI
U$3: 5VDC/5W; HLK-5M05
U$4, U$5, U$6, U$7, U$8, U$9, U$10, U$11: RELAYPTH; SRD-05VDC-SL-C
U$12: PCF8574P; DIL16
X1: MSTBA2
X2, X3, X4, X5, X6, X7, X8, X9: MSTBA3

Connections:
CSN: U$1.8, U$2.D10
GDO0: U$1.7, U$2.D2
GND: C1.-, CONFIG.1, IC1.9 (GND), IC2.1 (G1), IC2.10 (GND), IC2.19 (G2), LED5.A, S1.1, S2.1, S3.1, S4.1, S5.3 (2), S6.3 (2), S7.3 (2), S8.3 (2), SABOTAGE.1, U$1.2, U$2.GND, U$2.GND1 (GND2), U$3.3 (-VO), U$12.1 (A0), U$12.2 (A1), U$12.3 (A2), U$12.8 (GND)
unnamed: IC2.2 (A1), U$12.4 (P0)
unnamed: U$11.SWCOMMON, X9.2
unnamed: U$10.SWCOMMON, X8.2
unnamed: U$9.SWCOMMON, X7.2
unnamed: U$8.SWCOMMON, X6.2
unnamed: U$10.SWCLOSED (SWCLOSE), X8.1
unnamed: U$10.SWOPEN, X8.3
unnamed: U$11.SWCLOSED (SWCLOSE), X9.1
unnamed: F1.1, X1.1
unnamed: F2.1, U$3.4 (+VO)
unnamed: U$3.2 (2AC), X1.2
unnamed: S1.3 (2), U$2.D5
unnamed: S2.3 (2), U$2.D6
unnamed: S3.3 (2), U$2.D7
unnamed: S4.3 (2), U$2.D9
unnamed: CONFIG.3 (2), U$2.D8
unnamed: R5.1, U$2.D4
unnamed: LED5.K (C), R5.2
unnamed: F1.2, U$3.1 (1AC)
unnamed: SABOTAGE.2, U$2.D3
unnamed: U$6.SWCLOSED (SWCLOSE), X4.1
unnamed: U$7.SWCOMMON, X5.2
unnamed: U$6.SWOPEN, X4.3
unnamed: S5.1, U$2.A0
unnamed: U$7.SWCLOSED (SWCLOSE), X5.1
unnamed: U$6.SWCOMMON, X4.2
unnamed: U$7.SWOPEN, X5.3
unnamed: U$5.SWOPEN, X3.3
unnamed: U$5.SWCOMMON, X3.2
unnamed: U$5.SWCLOSED (SWCLOSE), X3.1
unnamed: U$4.SWOPEN, X2.3
unnamed: U$4.SWCOMMON, X2.2
unnamed: U$4.SWCLOSED (SWCLOSE), X2.1
unnamed: IC1.18 (O1), LED1.A, U$4.COIL1
unnamed: IC1.17 (O2), LED2.A, U$5.COIL1
unnamed: IC1.16 (O3), LED3.A, U$6.COIL1
unnamed: IC1.15 (O4), LED4.A, U$7.COIL1
unnamed: U$11.SWOPEN, X9.3
unnamed: U$9.SWOPEN, X7.3
unnamed: U$9.SWCLOSED (SWCLOSE), X7.1
unnamed: U$8.SWOPEN, X6.3
unnamed: U$8.SWCLOSED (SWCLOSE), X6.1
unnamed: IC1.14 (O5), LED6.A, U$8.COIL1
unnamed: IC1.13 (O6), LED7.A, U$9.COIL1
unnamed: IC1.12 (O7), LED8.A, U$10.COIL1
unnamed: IC1.11 (O8), LED9.A, U$11.COIL1
unnamed: IC1.1 (I1), IC2.18 (Y1)
unnamed: IC1.2 (I2), IC2.17 (Y2)
unnamed: IC1.3 (I3), IC2.16 (Y3)
unnamed: IC1.4 (I4), IC2.15 (Y4)
unnamed: IC1.5 (I5), IC2.14 (Y5)
unnamed: IC1.6 (I6), IC2.13 (Y6)
unnamed: IC1.7 (I7), IC2.12 (Y7)
unnamed: IC1.8 (I8), IC2.11 (Y8)
unnamed: LED1.K (C), R1.1
unnamed: LED2.K (C), R2.1
unnamed: LED3.K (C), R3.1
unnamed: LED4.K (C), R4.1
unnamed: LED6.K (C), R6.1
unnamed: LED7.K (C), R7.1
unnamed: LED8.K (C), R8.1
unnamed: LED9.K (C), R9.1
unnamed: U$2.A4, U$12.15 (SDA)
unnamed: U$2.A5, U$12.14 (SCL)
unnamed: S6.1, U$2.A1
unnamed: S7.1, U$2.A2
unnamed: S8.1, U$2.A3
unnamed: C1.+, U$1.1, U$2.VCC
unnamed: IC2.3 (A2), U$12.5 (P1)
unnamed: IC2.4 (A3), U$12.6 (P2)
unnamed: IC2.5 (A4), U$12.7 (P3)
unnamed: IC2.6 (A5), U$12.9 (P4)
unnamed: IC2.7 (A6), U$12.10 (P5)
unnamed: IC2.8 (A7), U$12.11 (P6)
unnamed: IC2.9 (A8), U$12.12 (P7)
SCLK: U$1.4, U$2.D13
SI: U$1.3, U$2.D11
SO: U$1.5, U$2.D12
VCC: F2.2, IC1.10 (CD+), IC2.20 (VCC), R1.2, R2.2, R3.2, R4.2, R6.2, R7.2, R8.2, R9.2, U$2.RAW, U$4.COIL0, U$5.COIL0, U$6.COIL0, U$7.COIL0, U$8.COIL0, U$9.COIL0, U$10.COIL0, U$11.COIL0, U$12.16 (VCC)

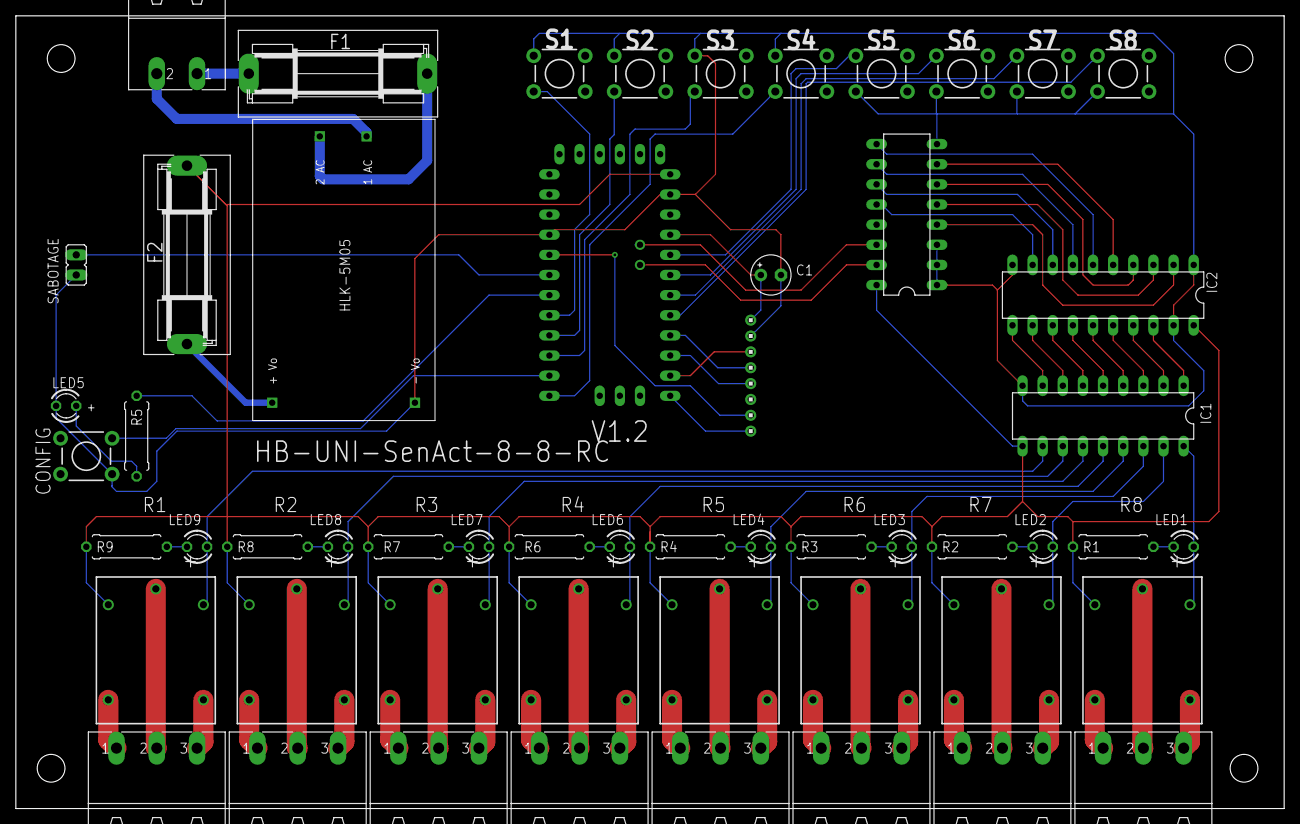
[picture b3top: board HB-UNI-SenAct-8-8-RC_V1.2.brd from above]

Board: 2 copper layers, 160.0 x 100.0 mm, 54 parts (0 on the bottom side), 82 nets.

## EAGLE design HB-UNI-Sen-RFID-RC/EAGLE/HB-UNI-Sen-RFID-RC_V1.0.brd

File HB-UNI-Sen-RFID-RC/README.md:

# HB-UNI-Sen-RFID-RC

+ HB-UNI-Sen-RFID-RC
	+ V1.0
		* Work 25%
		* 230VAC Version
		* Partlist not OK
	+ Work in progress !
>

### Partslist 230VAC Version
                    
  Part Name   |      PIC      |   Part Info   | Part Quantity |   Part Link 
------------- | ------------- | ------------- | ------------- | -------------
Arduino||Arduino Pro Mini 8Mhz 3.3V|1|[Links](https://de.aliexpress.com/item/32863952987.html?spm=a2g0s.9042311.0.0.27424c4d2YDzey)
CC1101||CC1101 Funkmodul|1|[Links](https://de.aliexpress.com/item/32924239954.html?spm=a2g0s.9042311.0.0.27424c4dO9ofu2)
Config,S1 - S4||Taster 6x6|5|[Links](https://de.aliexpress.com/item/32912263133.html?spm=a2g0s.9042311.0.0.2cb44c4dtuowdv)
LED1 - LED5||LED 3mm|5|[Links](https://de.aliexpress.com/item/32844298998.html?spm=a2g0s.9042311.0.0.27424c4dBW9kvr)
HLK-5M05||HLK-PM01|1|[Links](https://de.aliexpress.com/item/32705471039.html?spm=a2g0s.9042311.0.0.2cb44c4dtuowdv)
F1,F2||Sicherungshalter|2|[Links](https://de.aliexpress.com/item/32817849786.html?spm=a2g0o.productlist.0.0.260073beDSkClD&algo_pvid=51b52a6f-dc94-4152-9721-98bffea40076&algo_expid=51b52a6f-dc94-4152-9721-98bffea40076-1&btsid=c94e558f-368d-470b-a49c-61c69230d3d9&ws_ab_test=searchweb0_0,searchweb201602_2,searchweb201603_52)
R1 - R5||470 Ohm Widerstand|5|[Links](https://de.aliexpress.com/item/32475181535.html?spm=a2g0o.productlist.0.0.d4fa8034p2AKck&s=p&algo_pvid=4976c9e3-6165-4df4-b127-6d9845fdbe12&algo_expid=4976c9e3-6165-4df4-b127-6d9845fdbe12-1&btsid=7a52ff49-9ff4-47d2-965f-007ad481e8b7&ws_ab_test=searchweb0_0,searchweb201602_2,searchweb201603_52)
230V,S1 - S4||Wannenstecker für AKL 249, 2-pol, RM5,08|5|[Links](https://www.reichelt.de/wannenstecker-fuer-akl-249-2-pol-rm5-08-akl-230-02-p36701.html?)
RL1 - RL4||Wannenstecker für AKL 249, 3-pol, RM5,08|4|[Links](https://www.reichelt.de/wannenstecker-fuer-akl-249-3-pol-rm5-08-akl-230-03-p36702.html?)
RL1 - RL4||relais srd-05vdc|4|[Links](https://de.aliexpress.com/item/32695798177.html?spm=a2g0o.productlist.0.0.46db7659cuB4fB&algo_pvid=f16bd12e)
Arduino||Pin Header Streifen 12 Pin|2|[Links](https://de.aliexpress.com/item/32904918519.html?spm=a2g0s.9042311.0.0.27424c4dCsKCBi)
CC1101||Stiftleiste 20 polig, vergoldet, Raster 2,00mm|1|[Links](https://secure.reichelt.com/lu/de/stiftleiste-20-pol-vergoldet-bkl-10120400-p235635.html?)
C1||50V10UF|1|[Links](https://de.aliexpress.com/item/32741687066.html?spm=a2g0o.productlist.0.0.4d225216N68Cr1&algo_pvid=dbcb75f4-e623-4355-8aa4-ccd3a7b65d32&algo_expid=dbcb75f4-e623-4355-8aa4-ccd3a7b65d32-3&btsid=a9b8176e-1372-45d7-a781-8d3fc9fab8e5&ws_ab_test=searchweb0_0,searchweb201602_2,searchweb201603_52)
Sabotage,Arduino||Jumper|1|[Links](https://de.aliexpress.com/item/32873263301.html?spm=a2g0o.productlist.0.0.18ea263dluRsmQ&algo_pvid=b495ebad-e4de-4809-a086-8143c1f9f12b&algo_expid=b495ebad-e4de-4809-a086-8143c1f9f12b-2&btsid=53bb7c29-6fd7-4471-b8c4-bc2766b36d10&ws_ab_test=searchweb0_0,searchweb201602_2,searchweb201603_52)
RFID||RFID IC Drahtlose Modul SPI|1|[Links](https://de.aliexpress.com/item/2038558596.html?spm=a2g0s.9042311.0.0.27424c4djgizLc)
Buzzer||Aktive Summer 5V|1|[Links](https://de.aliexpress.com/item/32855755434.html?spm=a2g0s.9042311.0.0.27424c4dQGznlY)
-|-|-|-
OPTIONAL||FT232RL USB zu TTL Serielle Adapter|1|[Links](https://de.aliexpress.com/item/32846166237.html?spm=a2g0s.9042311.0.0.27424c4dQGznlY)

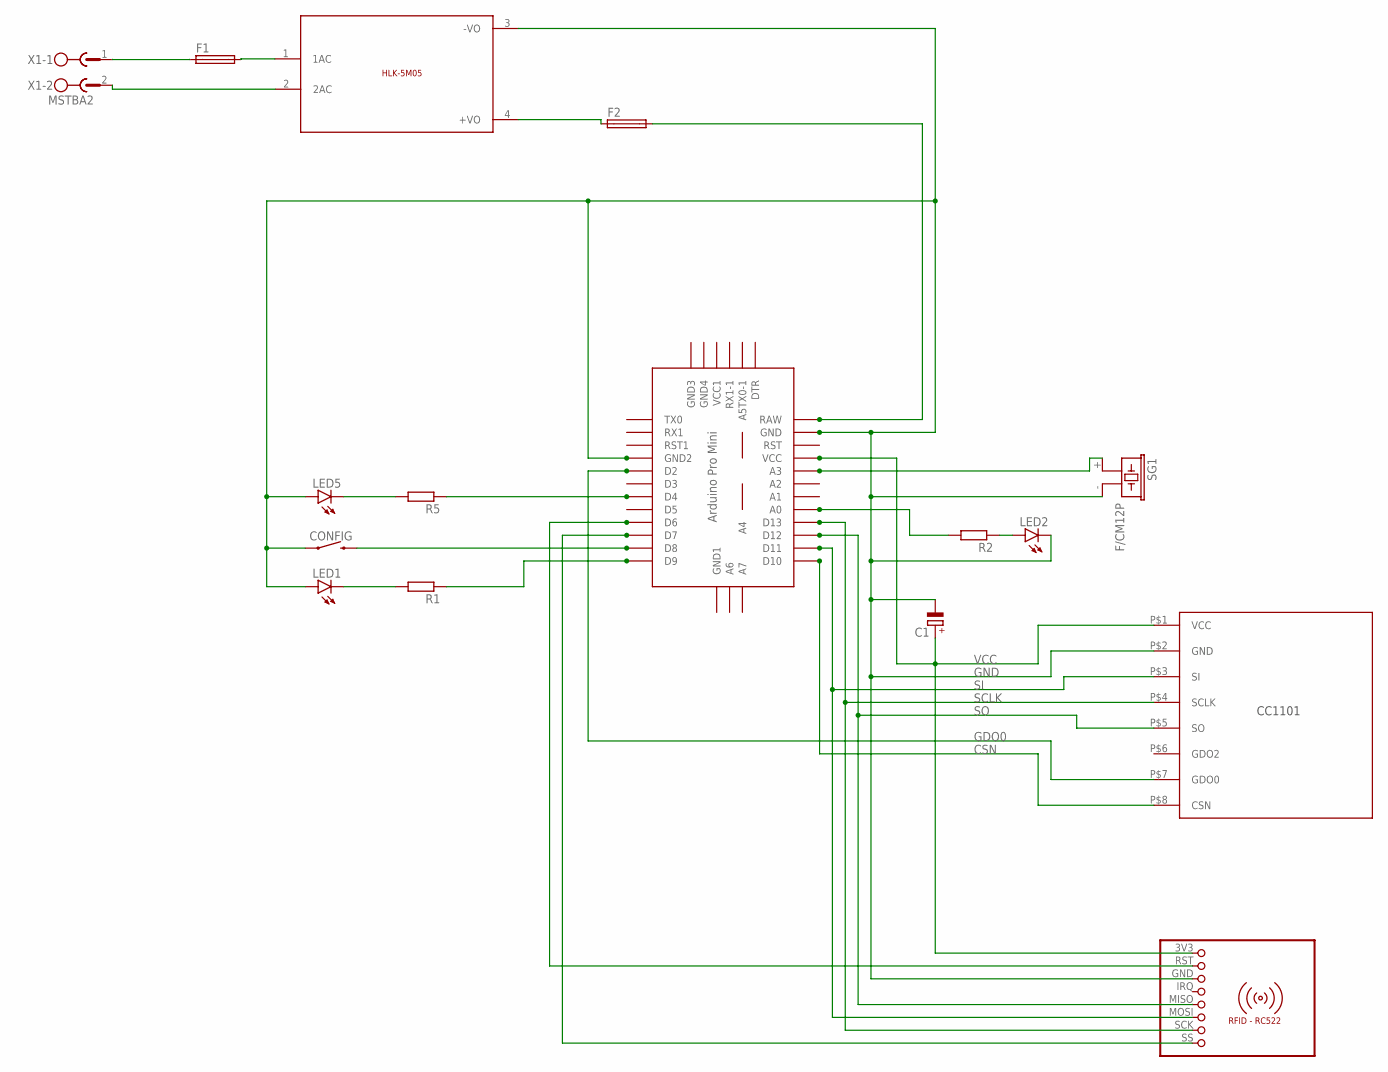
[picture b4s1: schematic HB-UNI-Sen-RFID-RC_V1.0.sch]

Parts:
C1: CPOL-EUE2.5-5; E2,5-5
CONFIG: MOMENTARY-SWITCH-SPST-PTH-6.0MM-KIT; TACTILE_SWITCH_PTH_6.0MM_KIT
F1, F2: SH22,5A
LED1, LED2, LED5: LED3MM
M1: RFID-RC522
R1, R2, R5: R-EU_0309/10; 0309/10
SG1: F/CM12P
U$1: CC1101
U$2: ABK-PRO-MINI
U$3: 5VDC/5W; HLK-5M05
X1: MSTBA2

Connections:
CSN: U$1.P$8 (CSN), U$2.D10
GDO0: U$1.P$7 (GDO0), U$2.D2
GND: C1.-, CONFIG.1, LED1.A, LED2.K (C), LED5.A, M1.GND (3), SG1.- (2), U$1.P$2 (GND), U$2.GND, U$2.GND1 (GND2), U$3.3 (-VO)
unnamed: M1.SS (8), U$2.D7
unnamed: M1.RST (2), U$2.D6
unnamed: LED1.K (C), R1.2
unnamed: R1.1, U$2.D9
unnamed: SG1.+ (1), U$2.A3
unnamed: LED2.A, R2.1
unnamed: R2.2, U$2.A0
unnamed: F1.1, X1.1
unnamed: F2.1, U$3.4 (+VO)
unnamed: U$3.2 (2AC), X1.2
unnamed: CONFIG.3 (2), U$2.D8
unnamed: R5.1, U$2.D4
unnamed: LED5.K (C), R5.2
unnamed: F1.2, U$3.1 (1AC)
unnamed: F2.2, U$2.RAW
SCLK: M1.SCK (7), U$1.P$4 (SCLK), U$2.D13
SI: M1.MOSI (6), U$1.P$3 (SI), U$2.D11
SO: M1.MISO (5), U$1.P$5 (SO), U$2.D12
VCC: C1.+, M1.3V3 (1), U$1.P$1 (VCC), U$2.VCC

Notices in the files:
parts and their libraries:
SparkFun-Switches: Licensing: Creative Commons ShareAlike 4.0 International - https://creativecommons.org/licenses/by-sa/4.0
